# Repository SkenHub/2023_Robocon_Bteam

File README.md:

# 2023_Robocon_Bteam
2023年高専ロボコン「もぎもぎ！フルーツＧＯラウンド」Bチーム
## メンバー
*  機械　ヒロハタ，金子，入谷，斉藤，神鍋 ,今井
*  制御　野口，川崎，笹渕，川口，黒住，佐谷  
*  回路　中井，岩井　
*  1年　北嶋，真志取  
* メイン：野口、川崎，金子
* ピット：渡邉，入谷，北嶋，廣畑，真志取

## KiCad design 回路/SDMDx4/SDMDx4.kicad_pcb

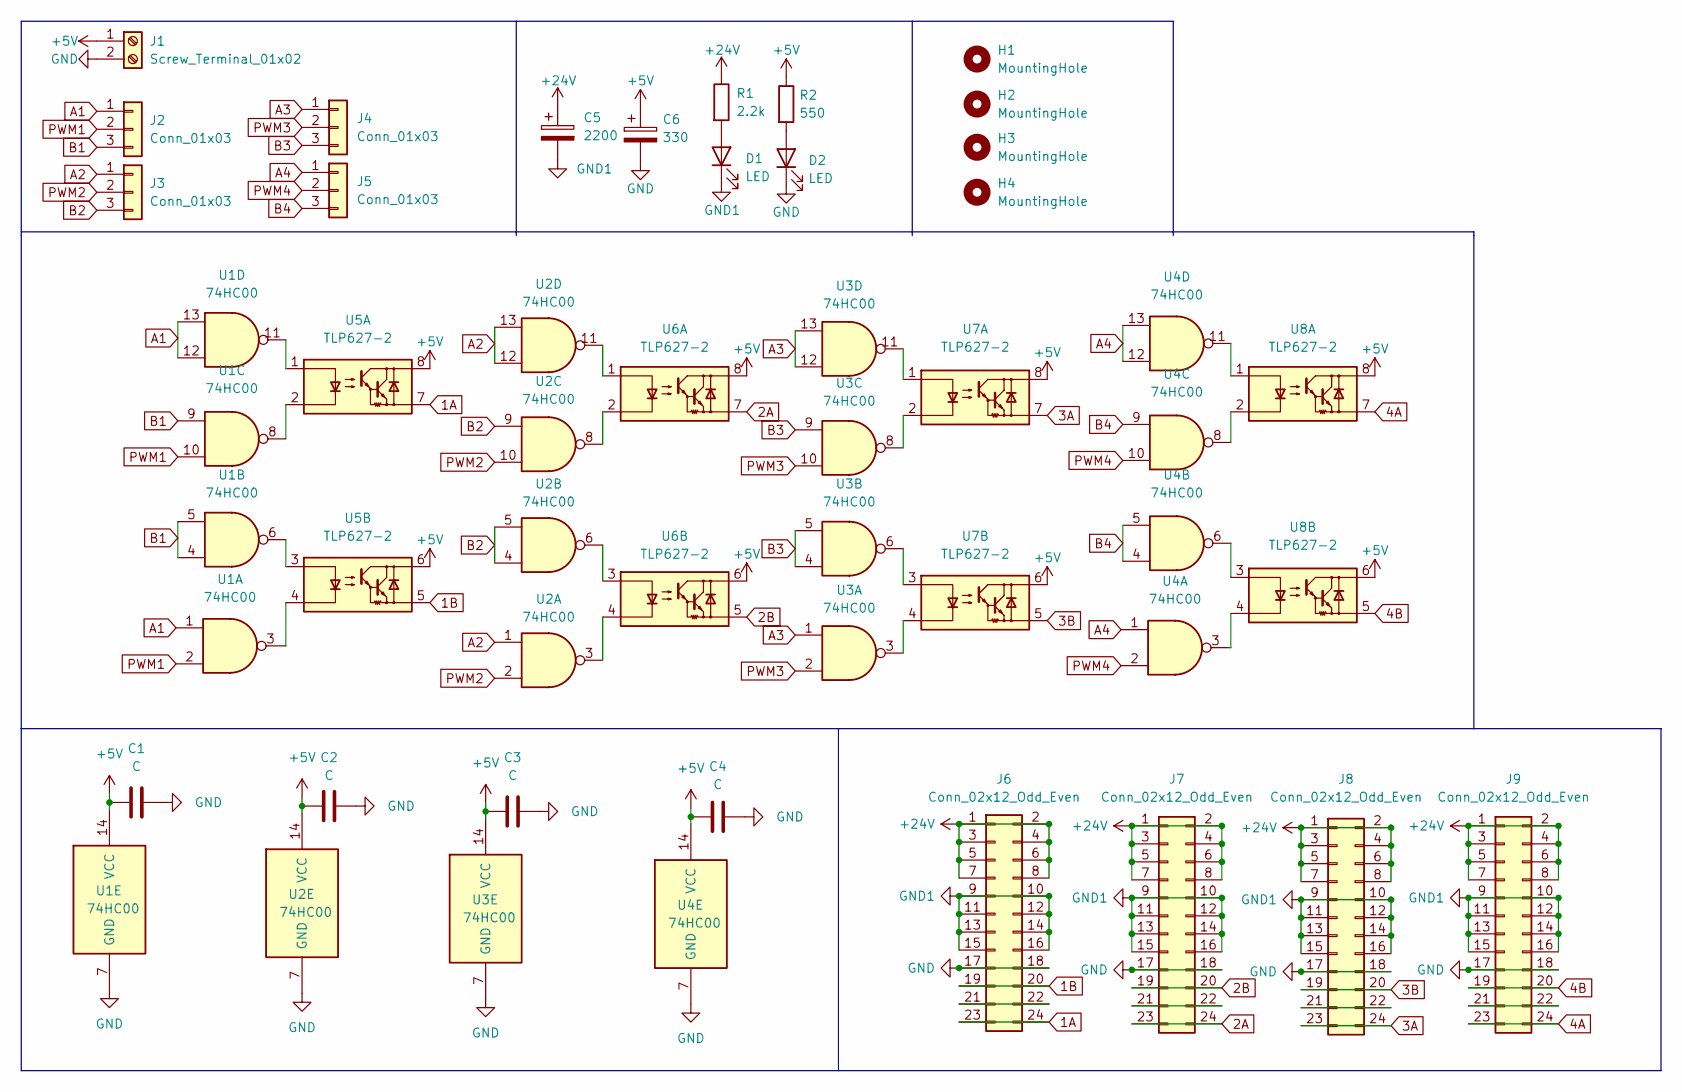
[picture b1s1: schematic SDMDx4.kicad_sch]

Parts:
C1, C2, C3, C4: C; C_Disc_D9.0mm_W2.5mm_P5.00mm
C5: 2200; CP_Radial_D10.0mm_P2.50mm_P5.00mm
C6: 330; CP_Radial_D5.0mm_P2.50mm
D1, D2: LED; LED_D3.0mm
H1, H2, H3, H4: MountingHole; MountingHole_3.2mm_M3
J1: Screw_Terminal_01x02; PinSocket_1x02_P2.54mm_Vertical
J2, J3, J4, J5: Conn_01x03; PinSocket_1x03_P2.54mm_Vertical
J6, J7, J8, J9: Conn_02x12_Odd_Even; PinHeader_2x12_P2.54mm_Vertical
R1: 2.2k; R_Axial_DIN0207_L6.3mm_D2.5mm_P10.16mm_Horizontal
R2: 550; R_Axial_DIN0207_L6.3mm_D2.5mm_P10.16mm_Horizontal
U1, U2, U3, U4: 74HC00; DIP-14_W7.62mm
U5, U6, U7, U8: TLP627-2; DIP-8_W7.62mm

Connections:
1A: J6.23, J6.24, U5.7
1B: J6.19, J6.20, U5.5
2A: J7.23, J7.24, U6.7
2B: J7.19, J7.20, U6.5
3A: J8.23, J8.24, U7.7
3B: J8.19, J8.20, U7.5
4A: J9.23, J9.24, U8.7
4B: J9.19, J9.20, U8.5
+5V: C1.1, C2.1, C3.1, C4.1, C6.1, J1.1, R2.1, U1.14 (VCC), U2.14 (VCC), U3.14 (VCC), U4.14 (VCC), U5.6, U5.8, U6.6, U6.8, U7.6, U7.8, U8.6, U8.8
+24V: C5.1, J6.1, J6.2, J6.3, J6.4, J6.5, J6.6, J6.7, J6.8, J7.1, J7.2, J7.3, J7.4, J7.5, J7.6, J7.7, J7.8, J8.1, J8.2, J8.3, J8.4, J8.5, J8.6, J8.7, J8.8, J9.1, J9.2, J9.3, J9.4, J9.5, J9.6, J9.7, J9.8, R1.1
A1: J2.1, U1.1, U1.12, U1.13
A2: J3.1, U2.1, U2.12, U2.13
A3: J4.1, U3.1, U3.12, U3.13
A4: J5.1, U4.1, U4.12, U4.13
B1: J2.3, U1.4, U1.5, U1.9
B2: J3.3, U2.4, U2.5, U2.9
B3: J4.3, U3.4, U3.5, U3.9
B4: J5.3, U4.4, U4.5, U4.9
GND: C1.2, C2.2, C3.2, C4.2, C6.2, D2.1 (K), J1.2, J6.17, J6.18, J7.17, J7.18, J8.17, J8.18, J9.17, J9.18, U1.7 (GND), U2.7 (GND), U3.7 (GND), U4.7 (GND)
GND1: C5.2, D1.1 (K), J6.9, J6.10, J6.11, J6.12, J6.13, J6.14, J6.15, J6.16, J7.9, J7.10, J7.11, J7.12, J7.13, J7.14, J7.15, J7.16, J8.9, J8.10, J8.11, J8.12, J8.13, J8.14, J8.15, J8.16, J9.9, J9.10, J9.11, J9.12, J9.13, J9.14, J9.15, J9.16
unnamed: J6.21, J6.22
unnamed: J7.21, J7.22
unnamed: J8.21, J8.22
unnamed: J9.21, J9.22
unnamed: D1.2 (A), R1.2
unnamed: D2.2 (A), R2.2
unnamed: U4.6, U8.3
unnamed: U4.8, U8.2
unnamed: U4.11, U8.1
unnamed: U1.11, U5.1
unnamed: U1.8, U5.2
unnamed: U1.6, U5.3
unnamed: U1.3, U5.4
unnamed: U2.11, U6.1
unnamed: U2.8, U6.2
unnamed: U2.6, U6.3
unnamed: U2.3, U6.4
unnamed: U3.11, U7.1
unnamed: U3.8, U7.2
unnamed: U3.6, U7.3
unnamed: U3.3, U7.4
unnamed: U4.3, U8.4
PWM1: J2.2, U1.2, U1.10
PWM2: J3.2, U2.2, U2.10
PWM3: J4.2, U3.2, U3.10
PWM4: J5.2, U4.2, U4.10

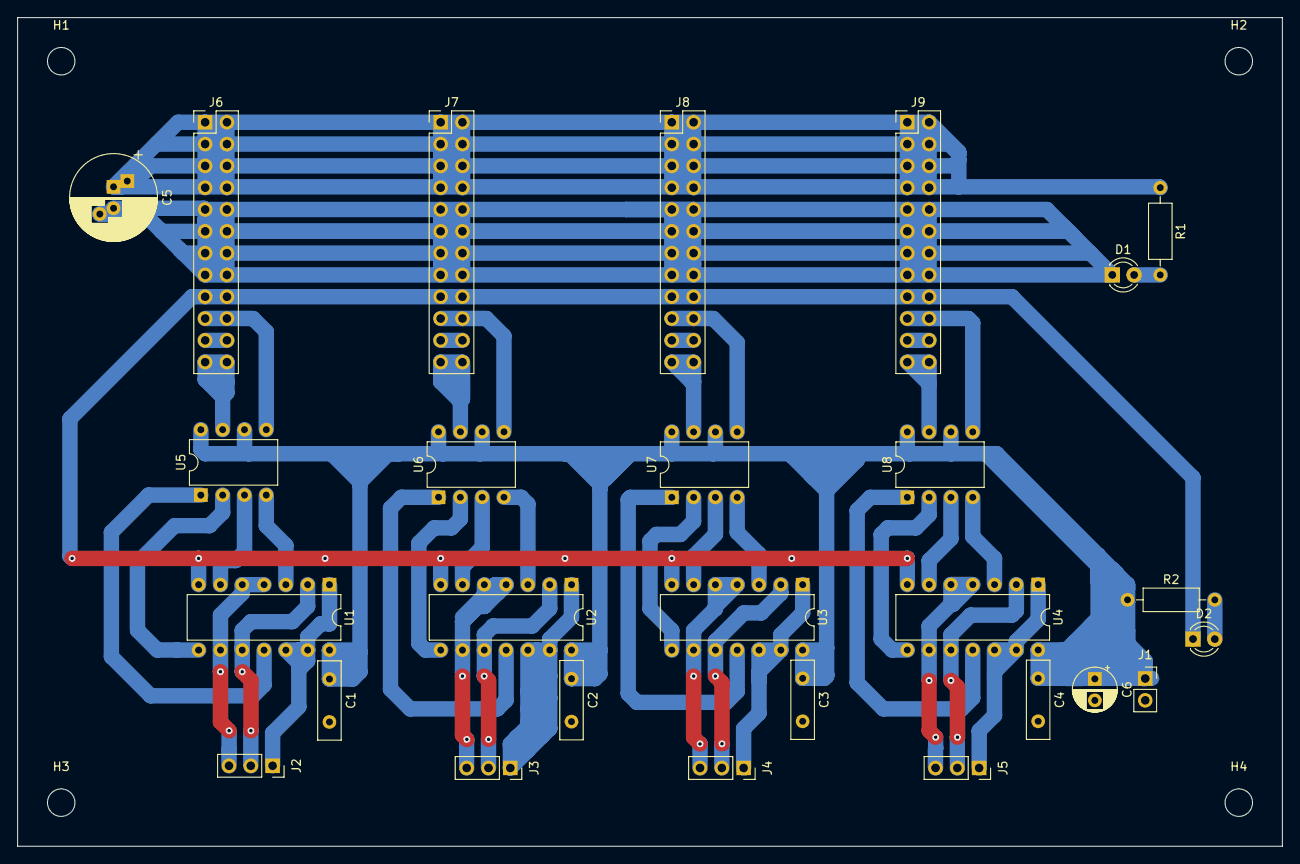
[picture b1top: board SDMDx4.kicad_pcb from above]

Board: 2 copper layers, 147.3 x 96.5 mm, 31 parts (0 on the bottom side), 46 nets.

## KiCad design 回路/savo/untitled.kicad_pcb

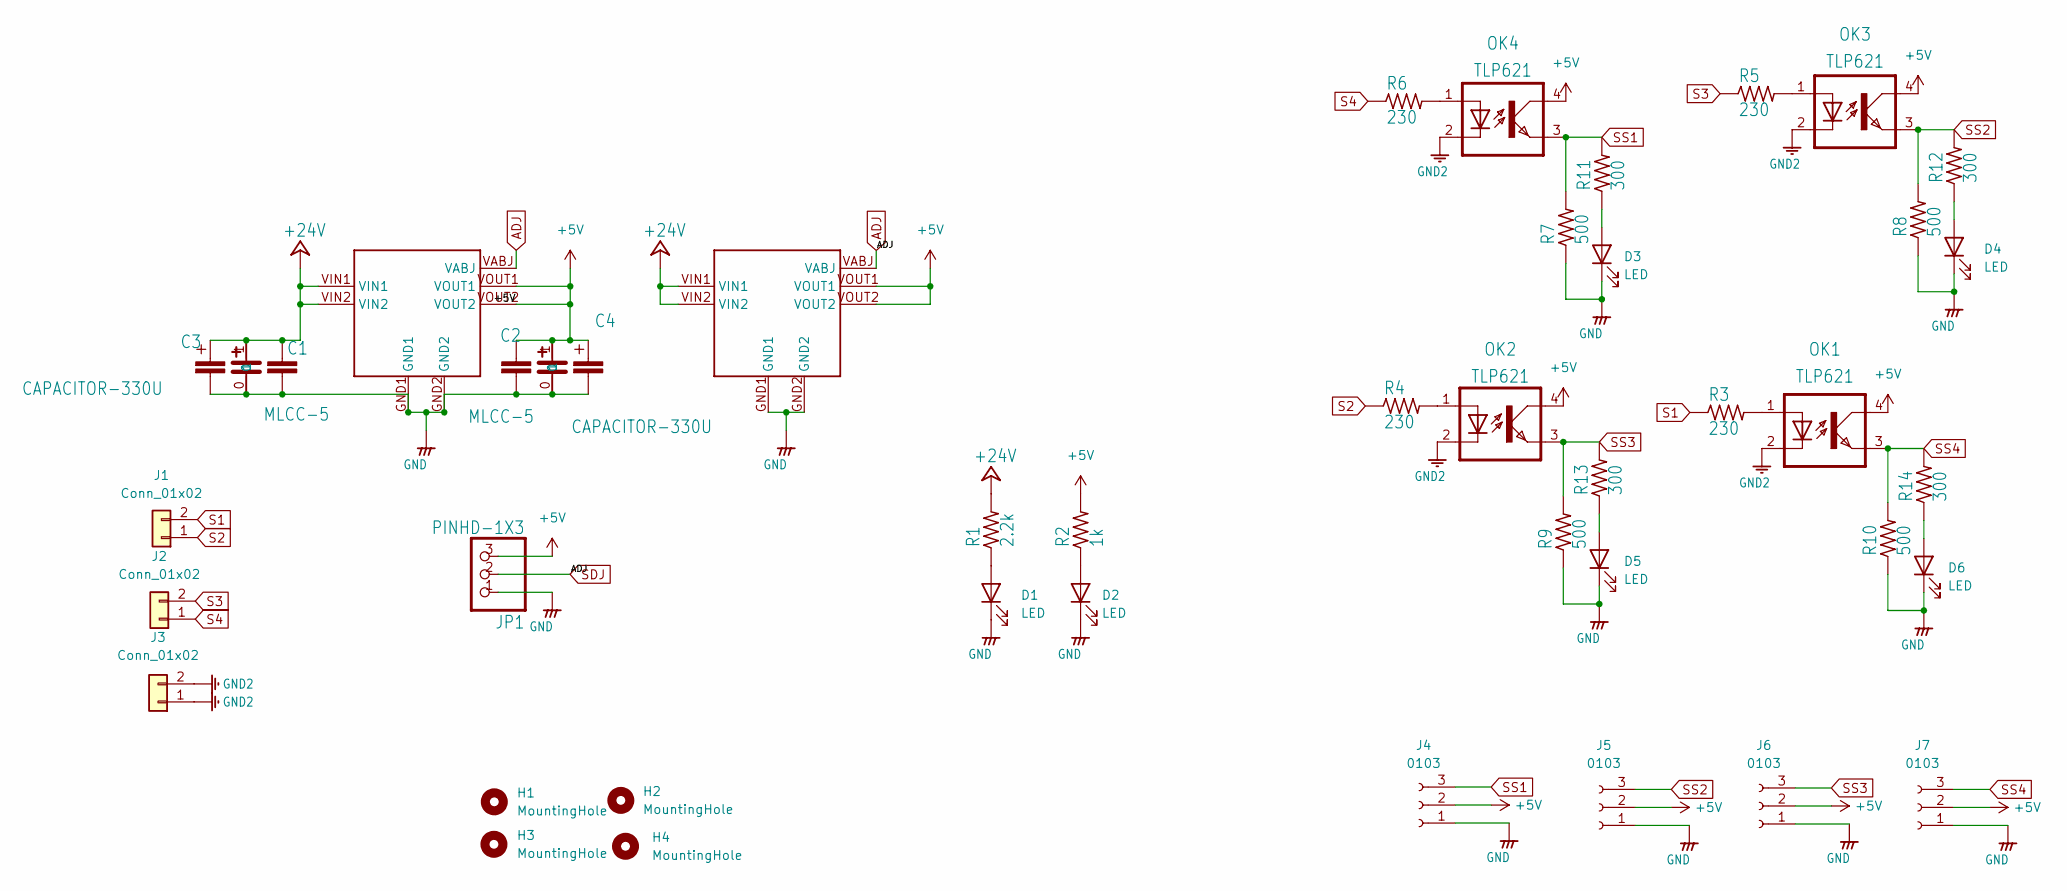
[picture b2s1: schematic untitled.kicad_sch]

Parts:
C1, C2: MLCC-5; MLCC_50
C3, C4: CAPACITOR-330U; C_330U
CAPACITOR1, CAPACITOR2: CAPACITOR
D1, D2, D3, D4, D5, D6: LED; LED_D3.0mm
H1, H2, H3, H4: MountingHole; MountingHole_3.2mm_M3
J1, J2, J3: Conn_01x02; PinHeader_1x02_P2.54mm_Vertical
J4, J5, J6, J7: 0103; FanPinHeader_1x03_P2.54mm_Vertical
JP1: PINHD-1X3; 1X03
KIC-1, KIC-2: KIC-053
OK1, OK2, OK3, OK4: TLP621; DIP4
R1: 2.2k; R_Axial_DIN0207_L6.3mm_D2.5mm_P10.16mm_Horizontal
R2: 1k; R_Axial_DIN0207_L6.3mm_D2.5mm_P10.16mm_Horizontal
R3, R4, R5, R6: 230; R_Axial_DIN0207_L6.3mm_D2.5mm_P10.16mm_Horizontal
R7, R8, R9, R10: 500; R_Axial_DIN0207_L6.3mm_D2.5mm_P10.16mm_Horizontal
R11, R12, R13, R14: 300; R_Axial_DIN0207_L6.3mm_D2.5mm_P10.16mm_Horizontal

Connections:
+5V: C2.1, C4.P$1 (1), CAPACITOR2.1, J4.2, J5.2, J6.2, J7.2, JP1.3, KIC-1.VOUT1, KIC-1.VOUT2, KIC-2.VOUT1, KIC-2.VOUT2, OK1.4 (COL), OK2.4 (COL), OK3.4 (COL), OK4.4 (COL), R2.2
+24V: C1.1, C3.P$1 (1), CAPACITOR1.1, KIC-1.VIN1, KIC-1.VIN2, KIC-2.VIN1, KIC-2.VIN2, R1.2
ADJ: JP1.2, KIC-1.VABJ, KIC-2.VABJ
GND: C1.2, C2.2, C3.P$2 (2), C4.P$2 (2), CAPACITOR1.0, CAPACITOR2.0, D1.1 (K), D2.1 (K), D3.1 (K), D4.1 (K), D5.1 (K), D6.1 (K), J4.1, J5.1, J6.1, J7.1, JP1.1, KIC-1.GND1, KIC-1.GND2, KIC-2.GND1, KIC-2.GND2, R7.1, R8.1, R9.1, R10.1
GND12: J3.1, J3.2, OK1.2 (C), OK2.2 (C), OK3.2 (C), OK4.2 (C)
unnamed: D1.2 (A), R1.1
unnamed: D2.2 (A), R2.1
unnamed: D3.2 (A), R11.1
unnamed: D4.2 (A), R12.1
unnamed: D5.2 (A), R13.1
unnamed: D6.2 (A), R14.1
unnamed: OK1.1 (A), R3.2
unnamed: OK3.1 (A), R5.2
unnamed: OK4.1 (A), R6.2
unnamed: OK2.1 (A), R4.2
S1: J1.2, R3.1
S2: J1.1, R4.1
S3: J2.2, R5.1
S4: J2.1, R6.1
SS1: J4.3, OK4.3 (EMIT), R7.2, R11.2
SS2: J5.3, OK3.3 (EMIT), R8.2, R12.2
SS3: J6.3, OK2.3 (EMIT), R9.2, R13.2
SS4: J7.3, OK1.3 (EMIT), R10.2, R14.2

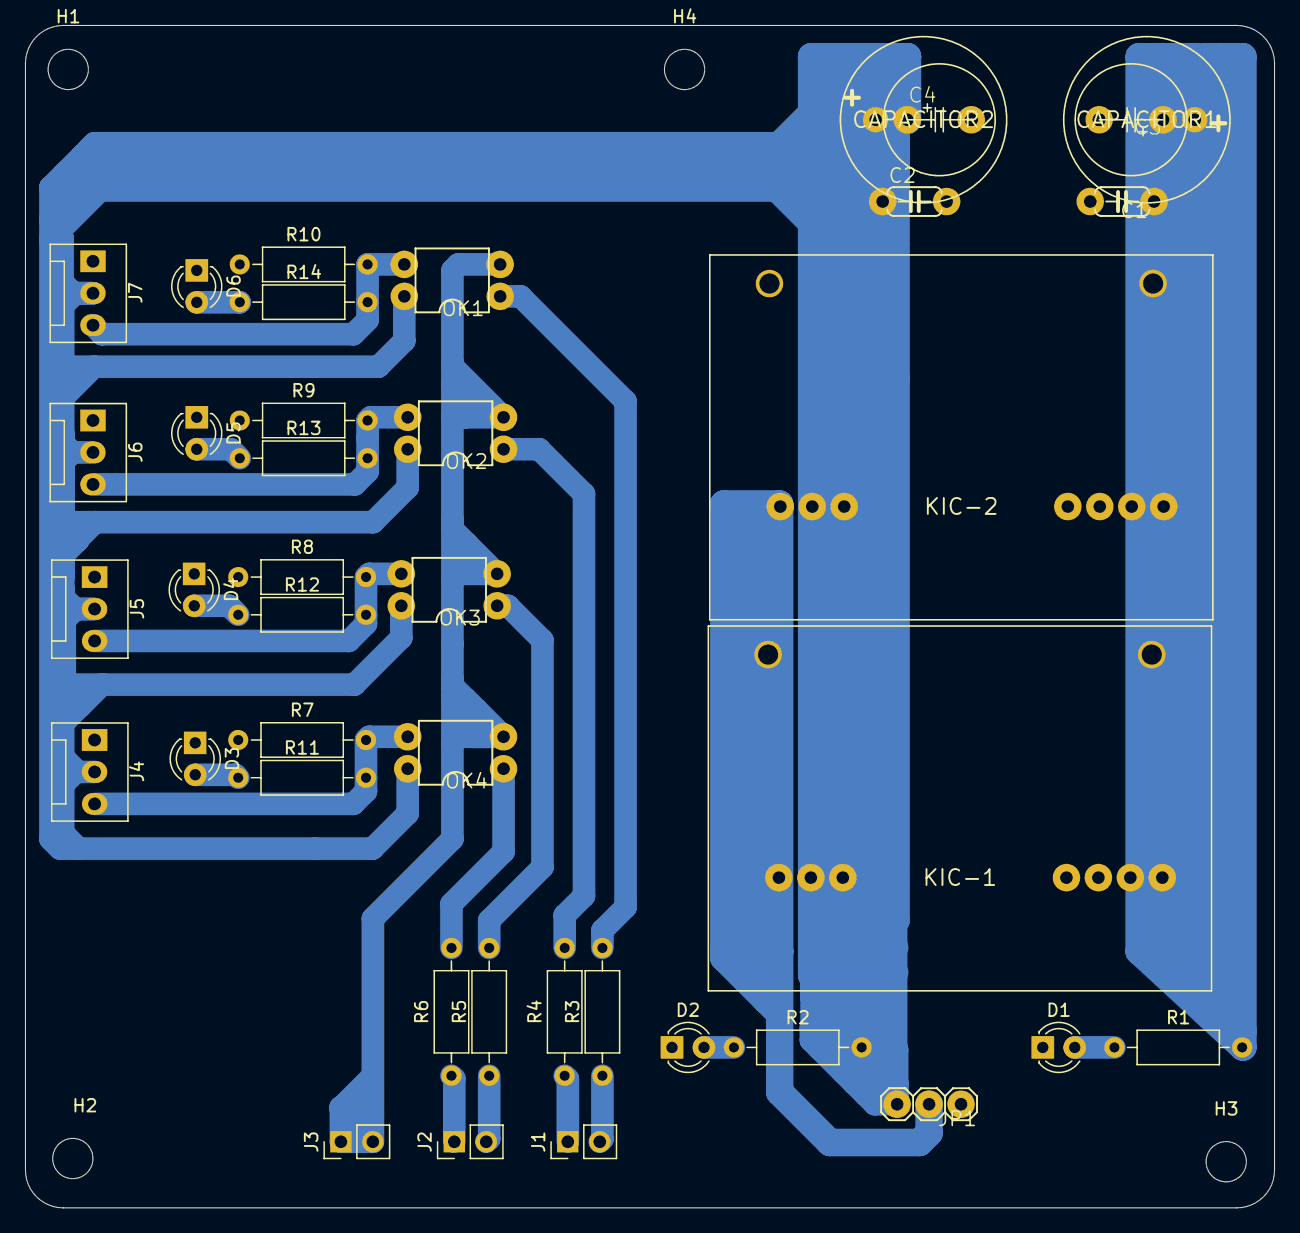
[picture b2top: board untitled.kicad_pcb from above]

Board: 2 copper layers, 99.3 x 94.0 mm, 44 parts (0 on the bottom side), 23 nets.

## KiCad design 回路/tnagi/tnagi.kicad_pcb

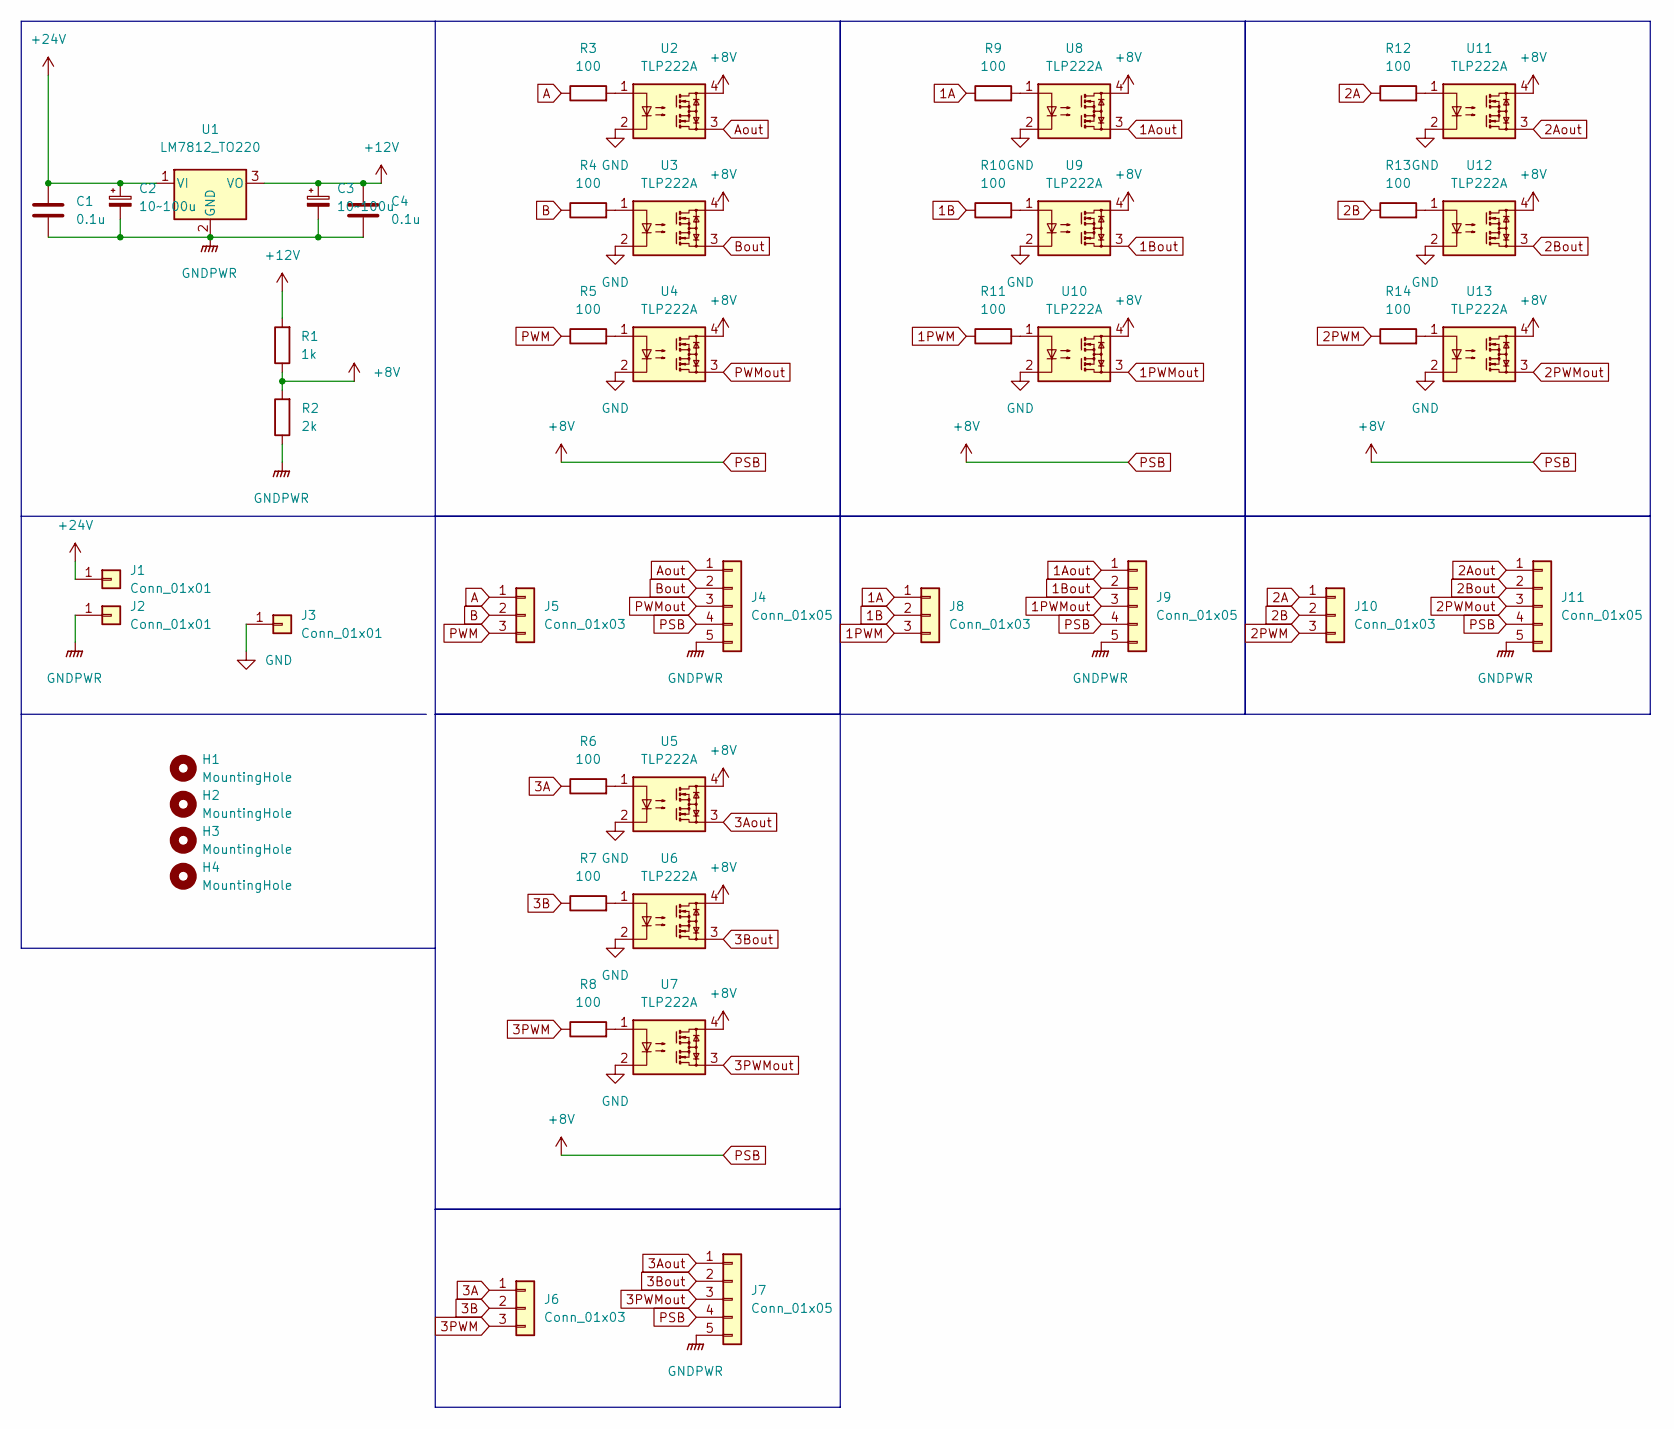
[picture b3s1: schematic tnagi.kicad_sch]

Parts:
C1, C4: 0.1u; C_Disc_D9.0mm_W2.5mm_P5.00mm
C2, C3: 10~100u; CP_Radial_D10.0mm_P5.00mm
H1, H2, H3, H4: MountingHole; MountingHole_3.2mm_M3
J1, J2, J3: Conn_01x01
J4, J7, J9, J11: Conn_01x05; PinSocket_1x05_P2.54mm_Vertical
J5, J6, J8, J10: Conn_01x03; PinSocket_1x03_P2.54mm_Vertical
R1: 1k; R_Axial_DIN0207_L6.3mm_D2.5mm_P10.16mm_Horizontal
R2: 2k; R_Axial_DIN0207_L6.3mm_D2.5mm_P10.16mm_Horizontal
R3, R4, R5, R6, R7, R8, R9, R10, R11, R12, R13, R14: 100; R_Axial_DIN0207_L6.3mm_D2.5mm_P10.16mm_Horizontal
U1: LM7812_TO220; TO-220-3_Vertical
U2, U3, U4, U5, U6, U7, U8, U9, U10, U11, U12, U13: TLP222A; DIP-4_W7.62mm

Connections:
1A: J8.1, R9.1
1Aout: J9.1, U8.3
1B: J8.2, R10.1
1Bout: J9.2, U9.3
1PWM: J8.3, R11.1
1PWMout: J9.3, U10.3
2A: J10.1, R12.1
2Aout: J11.1, U11.3
2B: J10.2, R13.1
2Bout: J11.2, U12.3
2PWM: J10.3, R14.1
2PWMout: J11.3, U13.3
3A: J6.1, R6.1
3Aout: J7.1, U5.3
3B: J6.2, R7.1
3Bout: J7.2, U6.3
3PWM: J6.3, R8.1
3PWMout: J7.3, U7.3
+12V: C3.1, C4.1, R1.2, U1.3 (VO)
+24V: C1.1, C2.1, J1.1, U1.1 (VI)
A: J5.1, R3.1
Aout: J4.1, U2.3
B: J5.2, R4.1
Bout: J4.2, U3.3
GND: J3.1, U2.2, U3.2, U4.2, U5.2, U6.2, U7.2, U8.2, U9.2, U10.2, U11.2, U12.2, U13.2
GNDPWR: C1.2, C2.2, C3.2, C4.2, J2.1, J4.5, J7.5, J9.5, J11.5, R2.1, U1.2 (GND)
unnamed: R3.2, U2.1
unnamed: R4.2, U3.1
unnamed: R5.2, U4.1
unnamed: R6.2, U5.1
unnamed: R7.2, U6.1
unnamed: R8.2, U7.1
unnamed: R9.2, U8.1
unnamed: R10.2, U9.1
unnamed: R11.2, U10.1
unnamed: R12.2, U11.1
unnamed: R13.2, U12.1
unnamed: R14.2, U13.1
PSB: J4.4, J7.4, J9.4, J11.4, R1.1, R2.2, U2.4, U3.4, U4.4, U5.4, U6.4, U7.4, U8.4, U9.4, U10.4, U11.4, U12.4, U13.4
PWM: J5.3, R5.1
PWMout: J4.3, U4.3

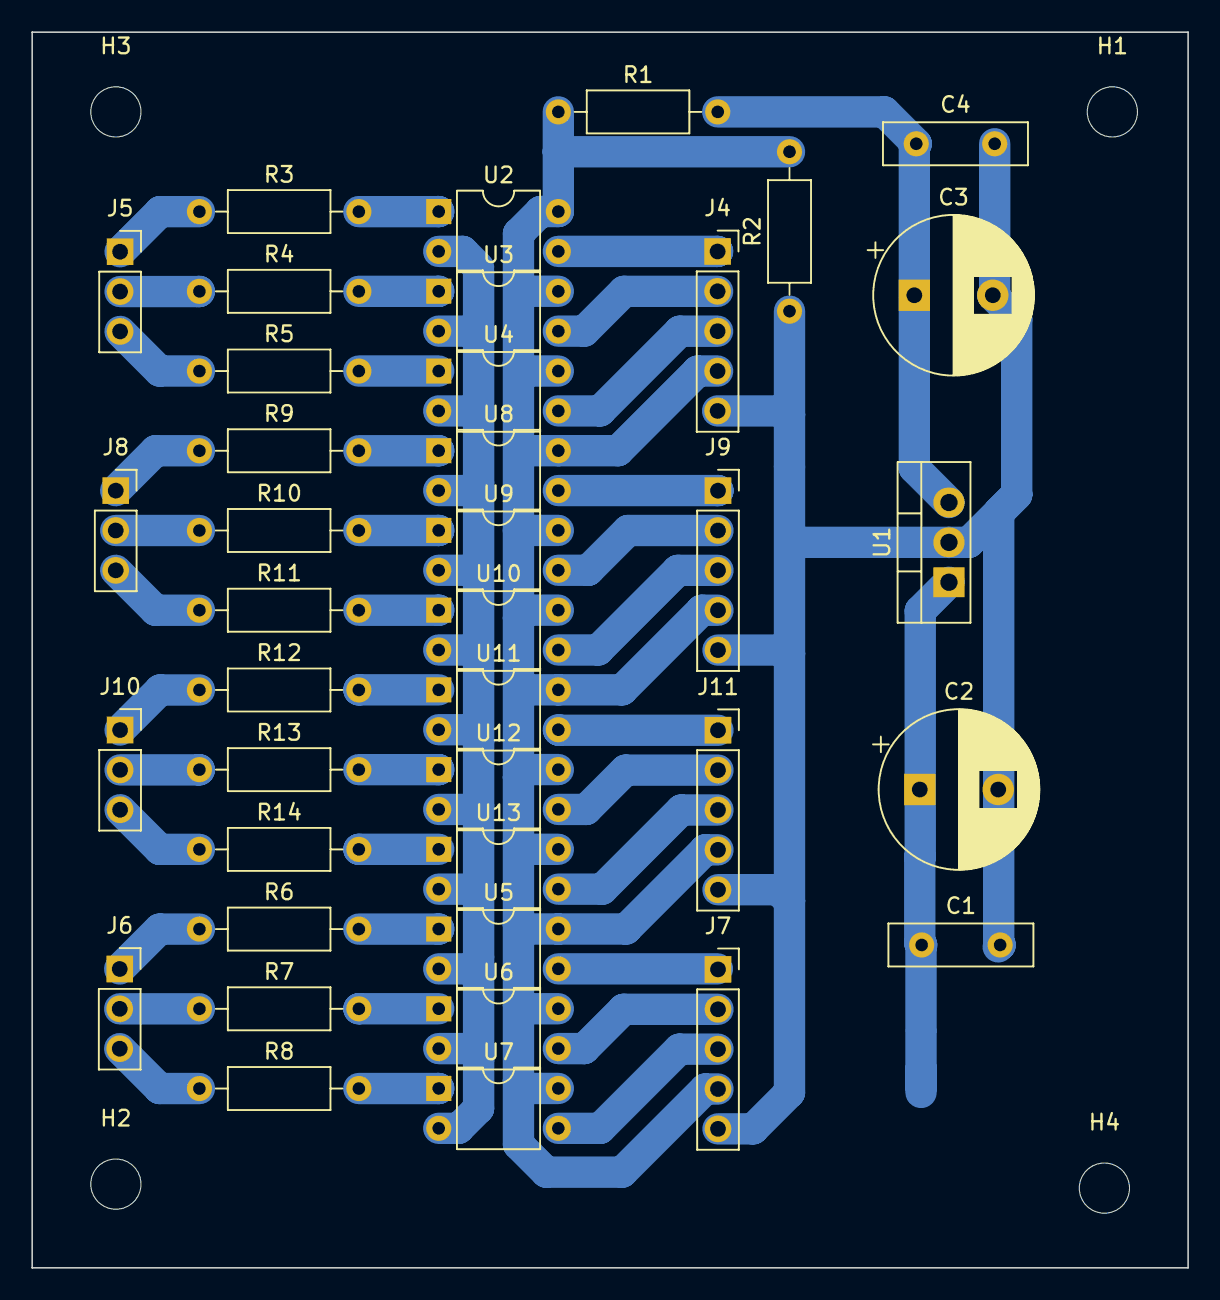
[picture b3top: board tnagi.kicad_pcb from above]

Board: 2 copper layers, 73.7 x 78.7 mm, 43 parts (0 on the bottom side), 41 nets.

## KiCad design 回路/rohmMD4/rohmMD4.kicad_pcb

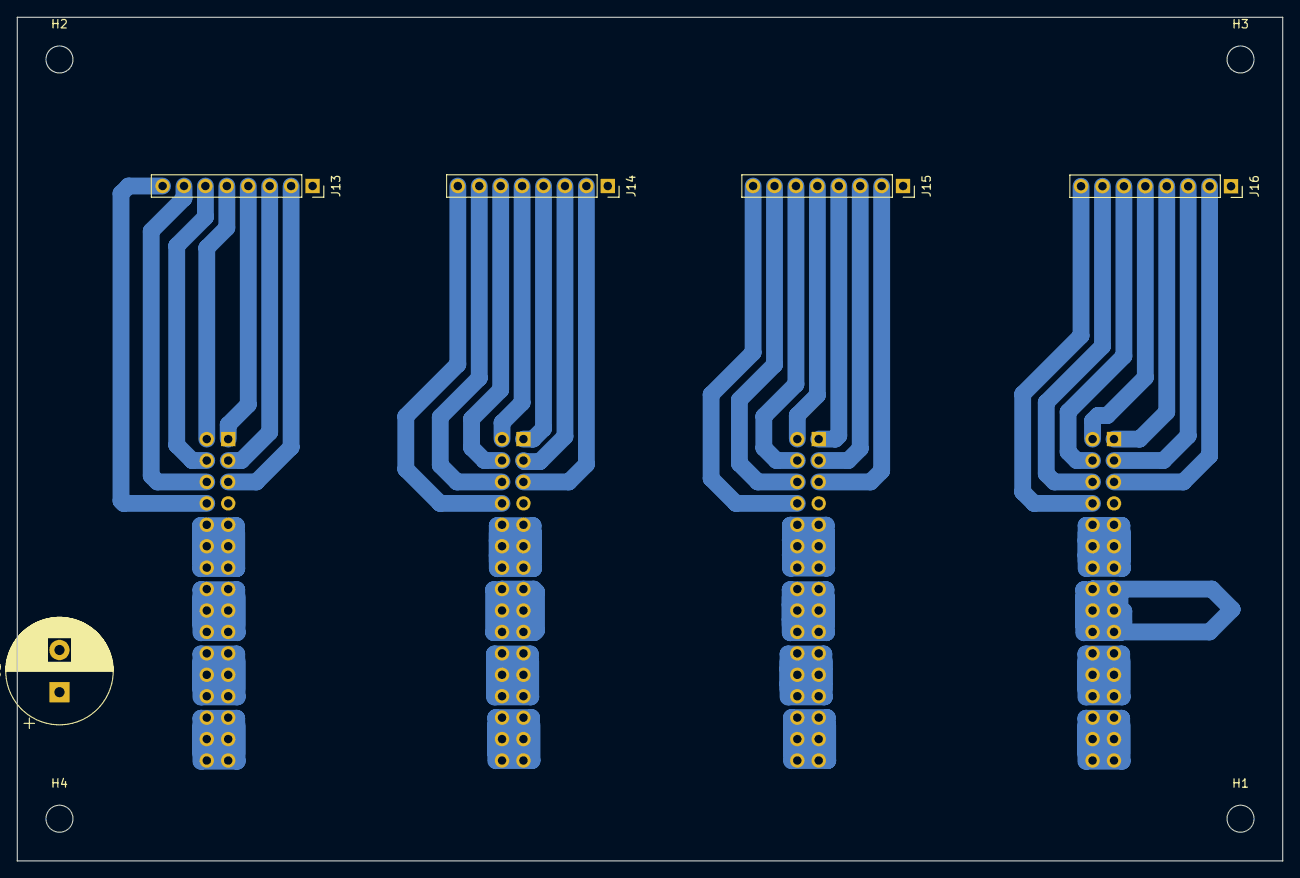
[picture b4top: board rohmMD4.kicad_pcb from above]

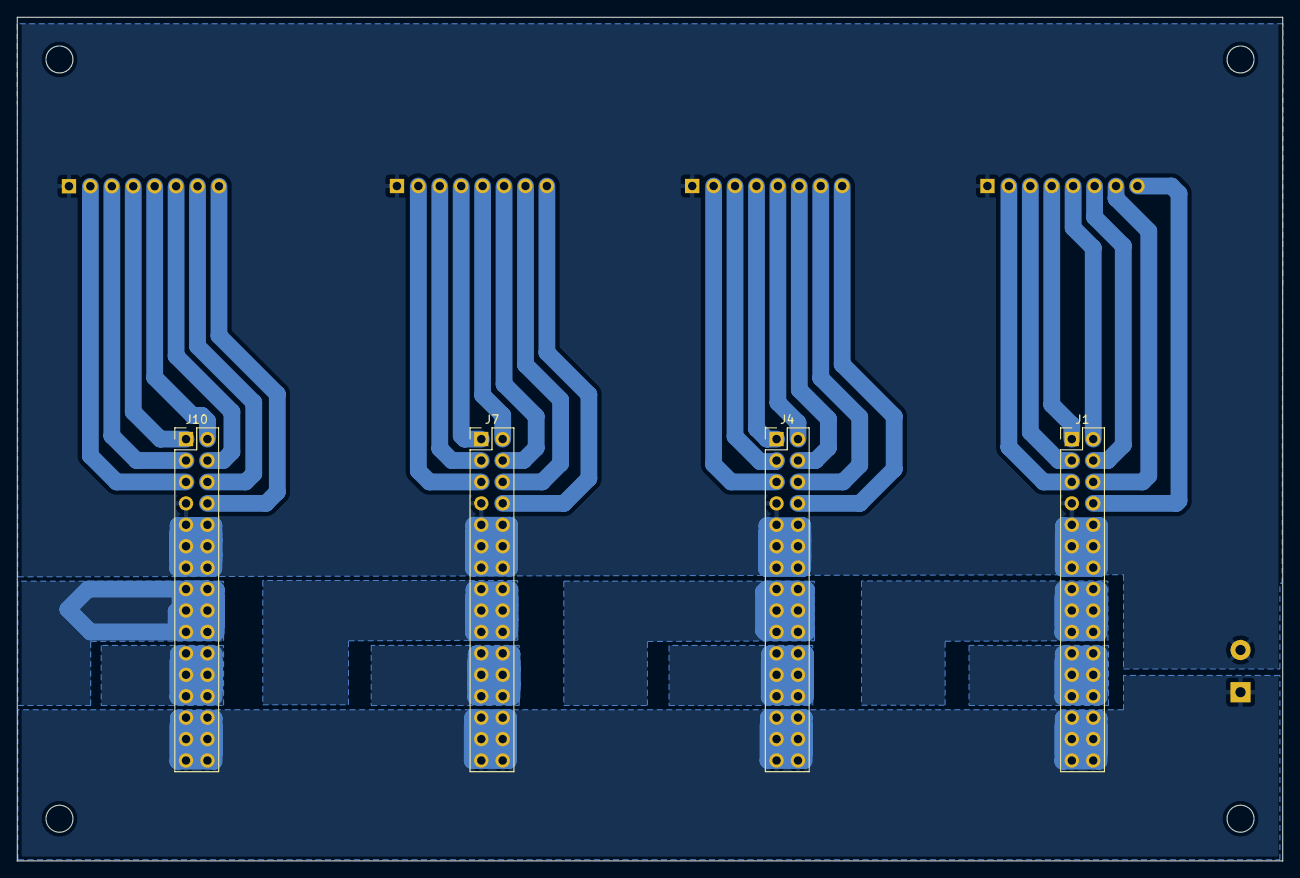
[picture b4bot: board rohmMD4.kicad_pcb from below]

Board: 2 copper layers, 150.0 x 100.0 mm, 13 parts (4 on the bottom side), 38 nets.

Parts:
C1: C_Polarized; CP_Radial_D12.5mm_P5.00mm
H1, H2, H3, H4: MountingHole; MountingHole_3.2mm_M3
J1, J4, J7, J10: Conn_02x16_Odd_Even; PinHeader_2x16_P2.54mm_Vertical
J13, J14, J15, J16: Conn_01x08; PinSocket_1x08_P2.54mm_Vertical

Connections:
1BRK: J1.3, J13.3
1FULL: J1.2, J13.5
1INA: J1.1, J13.4
1INB: J1.4, J13.6
1MA: J1.15, J1.16, J1.17, J1.18, J1.19, J1.20
1MB: J1.21, J1.22, J1.23, J1.24, J1.25, J1.26
1MOOD: J1.8, J13.8
1PSB: J1.5, J13.2
1PWM: J1.6, J13.7
2BRK: J4.3, J14.3
2FULL: J4.2, J14.5
2INA: J4.1, J14.4
2INB: J4.4, J14.6
2MA: J4.15, J4.16, J4.17, J4.18, J4.19, J4.20
2MB: J4.21, J4.22, J4.23, J4.24, J4.25, J4.26
2MOOD: J4.8, J14.8
2PSB: J4.5, J14.2
2PWM: J4.6, J14.7
3BRK: J7.3, J15.3
3FULL: J7.2, J15.5
3INA: J7.1, J15.4
3INB: J7.4, J15.6
3MA: J7.15, J7.16, J7.17, J7.18, J7.19, J7.20
3MB: J7.21, J7.22, J7.23, J7.24, J7.25, J7.26
3MOOD: J7.8, J15.8
3PSB: J7.5, J15.2
3PWM: J7.6, J15.7
4BRK: J10.3, J16.3
4FULL: J10.2, J16.5
4INA: J10.1, J16.4
4INB: J10.4, J16.6
4MA: J10.15, J10.16, J10.17, J10.18, J10.19, J10.20
4MB: J10.21, J10.22, J10.23, J10.24, J10.25, J10.26
4MOOD: J10.8, J16.8
4PSB: J10.5, J16.2
4PWM: J10.6, J16.7
+24V: C1.1, J1.27, J1.28, J1.29, J1.30, J1.31, J1.32, J4.27, J4.28, J4.29, J4.30, J4.31, J4.32, J7.27, J7.28, J7.29, J7.30, J7.31, J7.32, J10.27, J10.28, J10.29, J10.30, J10.31, J10.32
GND: C1.2, J1.7, J1.9, J1.10, J1.11, J1.12, J1.13, J1.14, J4.7, J4.9, J4.10, J4.11, J4.12, J4.13, J4.14, J7.7, J7.9, J7.10, J7.11, J7.12, J7.13, J7.14, J10.7, J10.9, J10.10, J10.11, J10.12, J10.13, J10.14, J13.1, J14.1, J15.1, J16.1

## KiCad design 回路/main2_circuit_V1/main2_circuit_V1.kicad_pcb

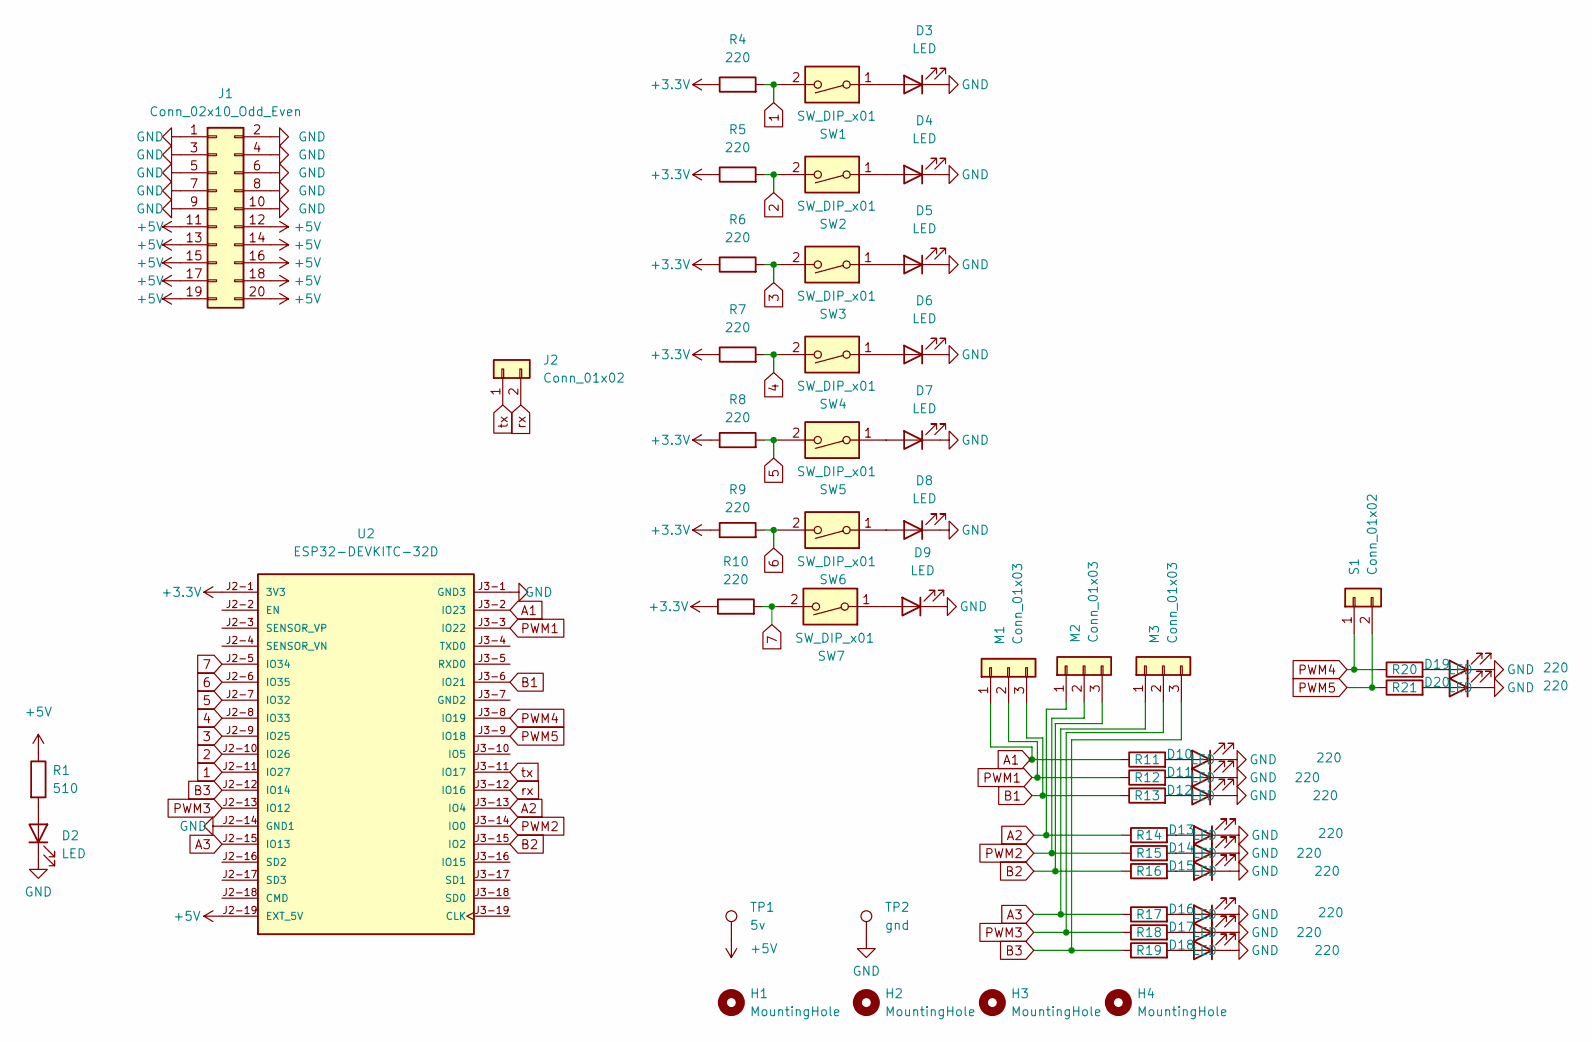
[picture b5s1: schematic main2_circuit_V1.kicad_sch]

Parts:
D2, D3, D4, D5, D6, D7, D8, D9, D10, D11, D12, D13, D14, D15, D16, D17, D18, D19, D20: LED; LED_D5.0mm
H1, H2, H3, H4: MountingHole; MountingHole_3.2mm_M3
J1: Conn_02x10_Odd_Even; PinHeader_2x10_P2.54mm_Vertical
J2: Conn_01x02; PinHeader_1x02_P2.54mm_Vertical
M1, M2, M3: Conn_01x03; PinHeader_1x03_P2.54mm_Vertical
R1: 510; R_Axial_DIN0207_L6.3mm_D2.5mm_P10.16mm_Horizontal
R4, R5, R6, R7, R8, R9, R10, R11, R12, R13, R14, R15, R16, R17, R18, R19, R20, R21: 220; R_Axial_DIN0207_L6.3mm_D2.5mm_P10.16mm_Horizontal
S1: Conn_01x02; PinHeader_1x02_P2.54mm_Vertical
SW1, SW2, SW3, SW4, SW5, SW6, SW7: SW_DIP_x01; PinHeader_1x02_P2.54mm_Vertical
TP1: 5v; TestPoint_THTPad_D2.0mm_Drill1.0mm
TP2: gnd; TestPoint_THTPad_D2.0mm_Drill1.0mm
U2: ESP32-DEVKITC-32D; MODULE_ESP32-DEVKITC-32D; PARTREV V4

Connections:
1: R4.2, SW1.2, U2.J2-11 (IO27)
2: R5.2, SW2.2, U2.J2-10 (IO26)
3: R6.2, SW3.2, U2.J2-9 (IO25)
4: R7.2, SW4.2, U2.J2-8 (IO33)
5: R8.2, SW5.2, U2.J2-7 (IO32)
6: R9.2, SW6.2, U2.J2-6 (IO35)
7: R10.2, SW7.2, U2.J2-5 (IO34)
+3.3V: R4.1, R5.1, R6.1, R7.1, R8.1, R9.1, R10.1, U2.J2-1 (3V3)
+5V: J1.11, J1.12, J1.13, J1.14, J1.15, J1.16, J1.17, J1.18, J1.19, J1.20, R1.1, TP1.1, U2.J2-19 (EXT_5V)
A1: M1.1, R11.1, U2.J3-2 (IO23)
A2: M2.1, R14.1, U2.J3-13 (IO4)
A3: M3.1, R17.1, U2.J2-15 (IO13)
B1: M1.3, R13.1, U2.J3-6 (IO21)
B2: M2.3, R16.1, U2.J3-15 (IO2)
B3: M3.3, R19.1, U2.J2-12 (IO14)
GND: D2.1 (K), D3.1 (K), D4.1 (K), D5.1 (K), D6.1 (K), D7.1 (K), D8.1 (K), D9.1 (K), D10.1 (K), D11.1 (K), D12.1 (K), D13.1 (K), D14.1 (K), D15.1 (K), D16.1 (K), D17.1 (K), D18.1 (K), D19.1 (K), D20.1 (K), J1.1, J1.2, J1.3, J1.4, J1.5, J1.6, J1.7, J1.8, J1.9, J1.10, TP2.1, U2.J2-14 (GND1), U2.J3-1 (GND3)
unnamed: D2.2 (A), R1.2
unnamed: D3.2 (A), SW1.1
unnamed: D4.2 (A), SW2.1
unnamed: D5.2 (A), SW3.1
unnamed: D6.2 (A), SW4.1
unnamed: D7.2 (A), SW5.1
unnamed: D8.2 (A), SW6.1
unnamed: D9.2 (A), SW7.1
unnamed: D10.2 (A), R11.2
unnamed: D11.2 (A), R12.2
unnamed: D12.2 (A), R13.2
unnamed: D13.2 (A), R14.2
unnamed: D14.2 (A), R15.2
unnamed: D15.2 (A), R16.2
unnamed: D16.2 (A), R17.2
unnamed: D17.2 (A), R18.2
unnamed: D18.2 (A), R19.2
unnamed: D19.2 (A), R20.2
unnamed: D20.2 (A), R21.2
PWM1: M1.2, R12.1, U2.J3-3 (IO22)
PWM2: M2.2, R15.1, U2.J3-14 (IO0)
PWM3: M3.2, R18.1, U2.J2-13 (IO12)
PWM4: R20.1, S1.1, U2.J3-8 (IO19)
PWM5: R21.1, S1.2, U2.J3-9 (IO18)
rx: J2.2, U2.J3-12 (IO16)
tx: J2.1, U2.J3-11 (IO17)

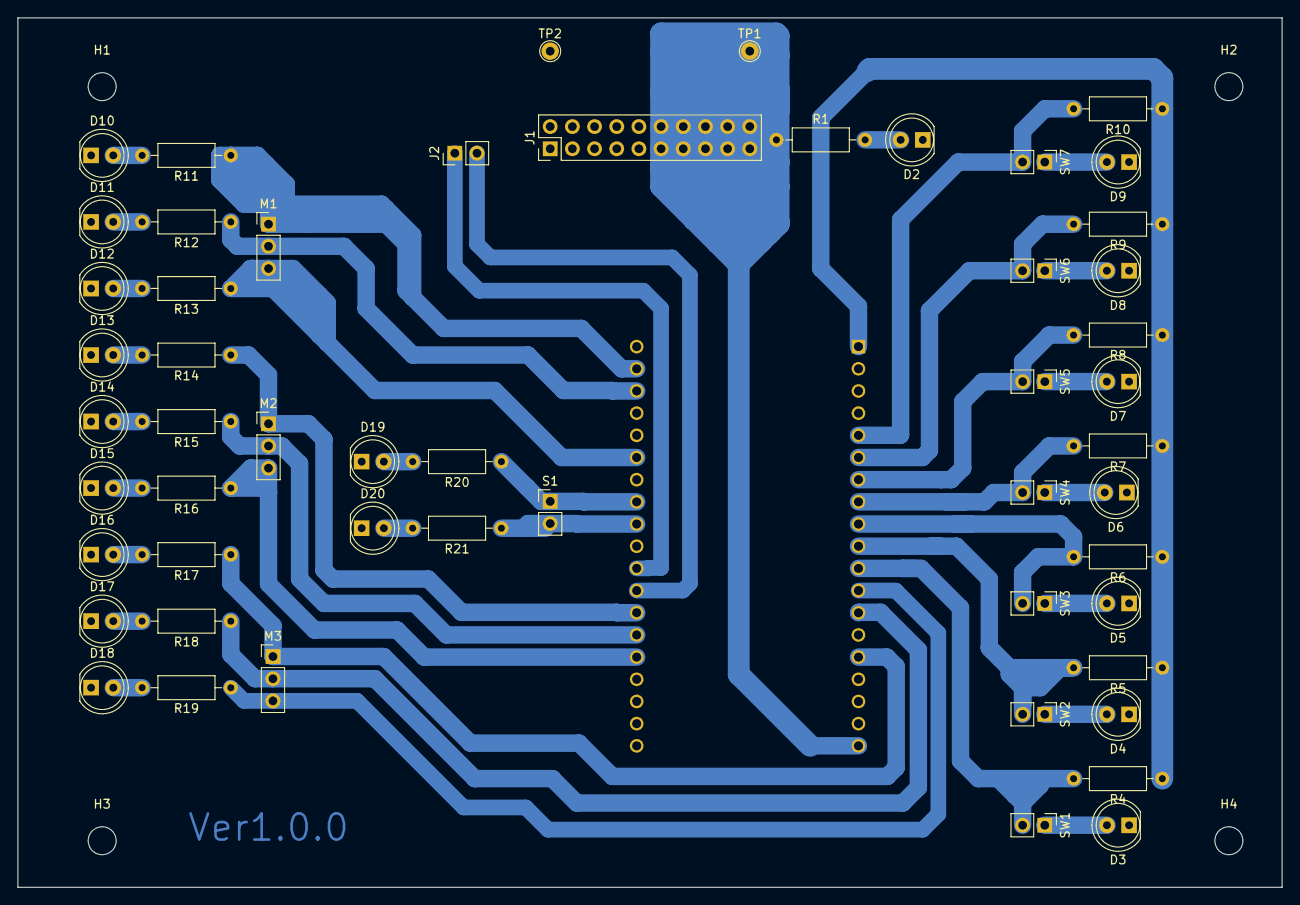
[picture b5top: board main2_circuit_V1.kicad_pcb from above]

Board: 2 copper layers, 144.8 x 99.6 mm, 58 parts (1 on the bottom side), 42 nets.
